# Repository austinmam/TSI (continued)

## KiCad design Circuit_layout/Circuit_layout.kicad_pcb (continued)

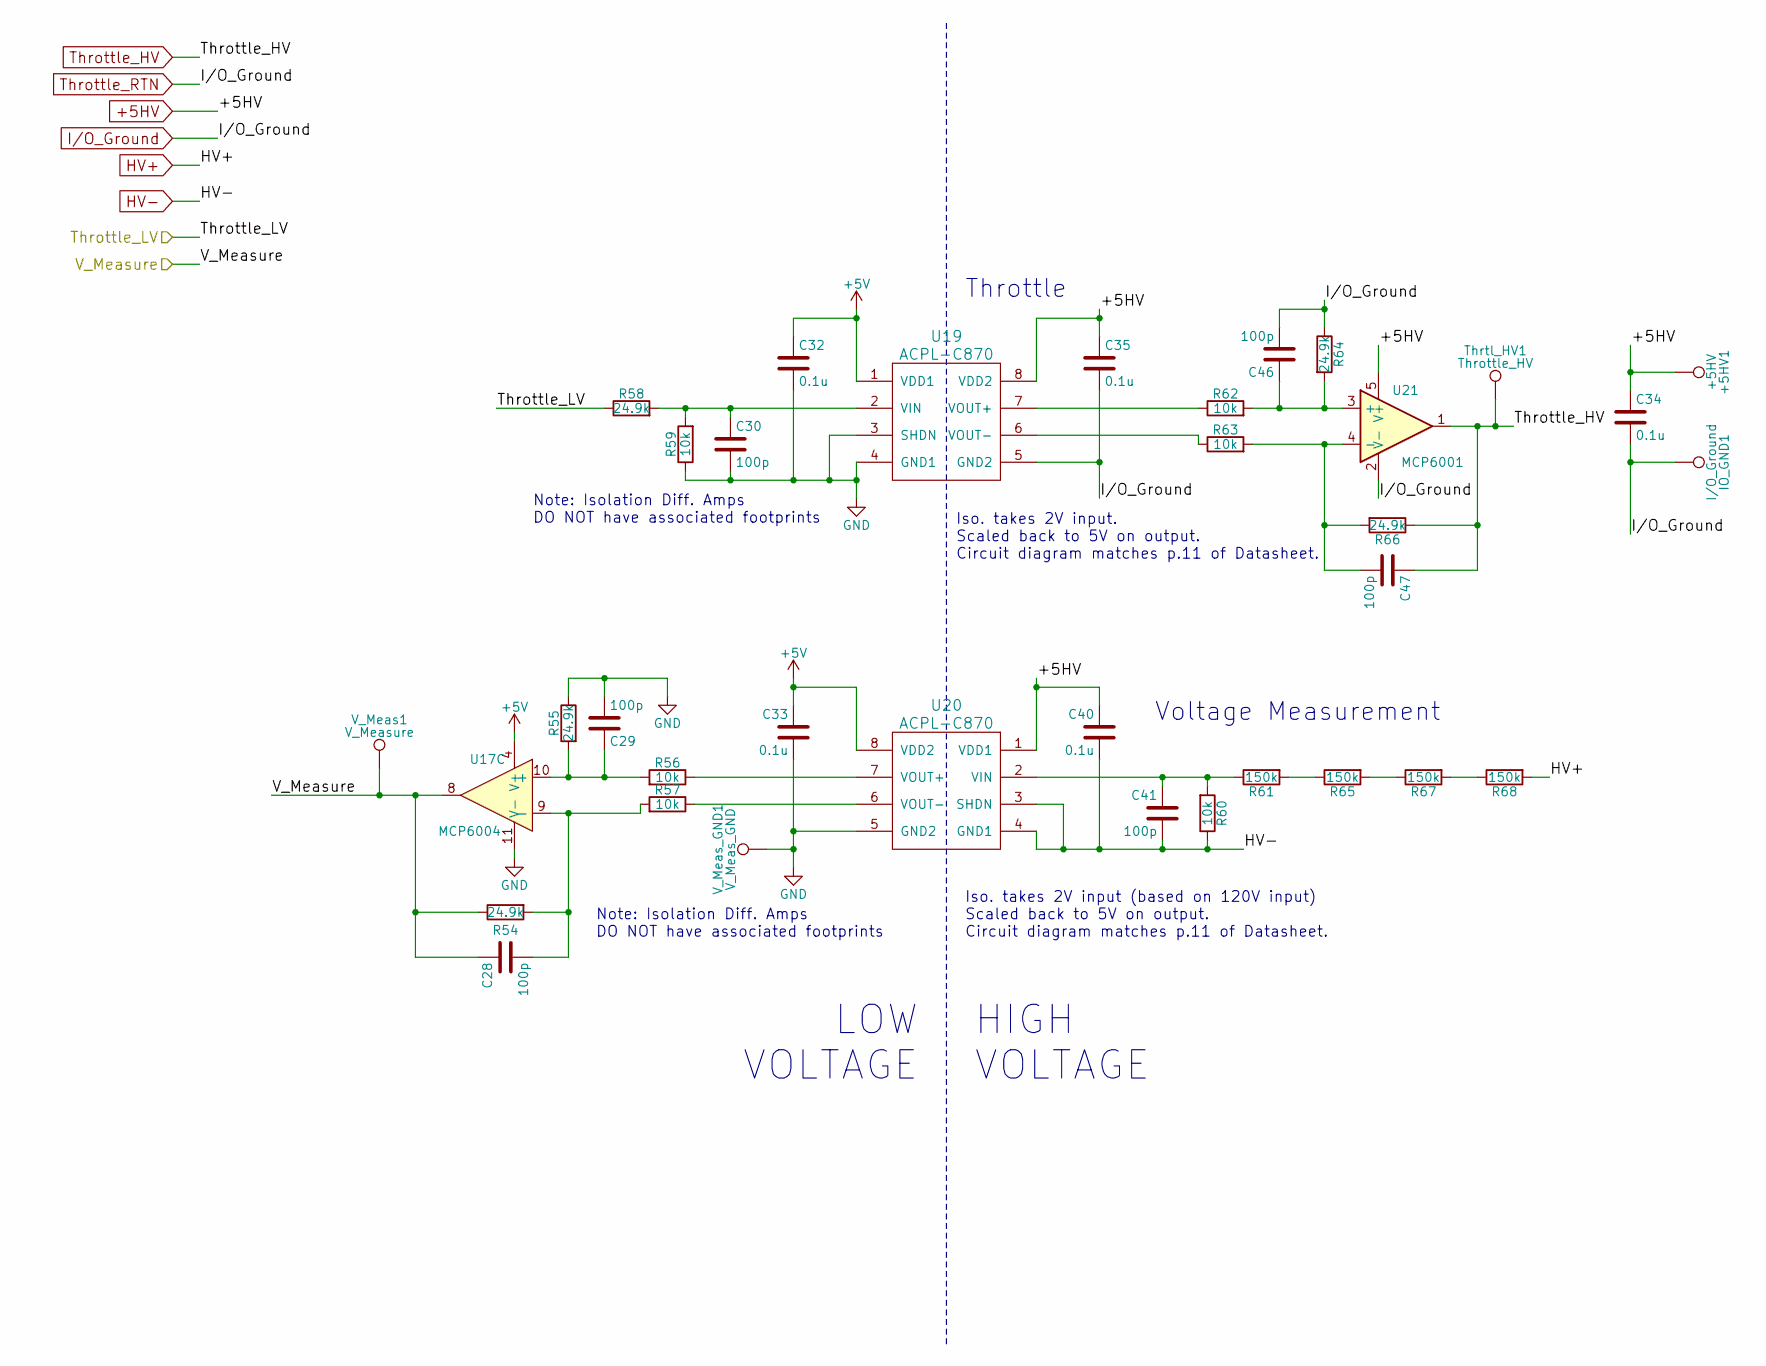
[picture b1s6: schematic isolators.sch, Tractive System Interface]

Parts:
+5HV1: +5HV; Measurement_Point_Round-SMD-Pad_Big
C28, C29, C30, C41, C46, C47: 100p; C_0805_HandSoldering; DigiKey P/N 399-1122-1-ND
C32, C33, C34, C35, C40: 0.1u; C_0805_HandSoldering; Digikey P/N 399-1168-1-ND
IO_GND1: I/O_Ground; Measurement_Point_Round-SMD-Pad_Big
R54, R55, R58, R64, R66: 24.9k; R_0805_HandSoldering; DigiKey P/N P24.9KCCT-ND
R56, R57, R59, R60, R62, R63: 10k; R_0805_HandSoldering; DigiKey P/N P10.0KCCT-ND
R61, R65, R67, R68: 150k; R_0805_HandSoldering; DigiKey P/N P150KCCT-ND
Thrtl_HV1: Throttle_HV; Measurement_Point_Round-SMD-Pad_Big
U17: MCP6004; SOIC-14_3.9x8.7mm_Pitch1.27mm; Digikey P/N MCP6004T-I/SLCT-ND
U19, U20: ACPL-C870; Iso_Diff_Amp_ACPL; Digikey P/N 516-2578-5-ND
U21: MCP6001; SOT-23-5_HandSoldering; DigiKey P/N MCP6001T-I/OTCT-ND
V_Meas1: V_Measure; Measurement_Point_Round-SMD-Pad_Big
V_Meas_GND1: V_Meas_GND; Measurement_Point_Square-SMD-Pad_Big

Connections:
+5HV: +5HV1.1, C34.1, C35.1, C40.1, U19.8 (VDD2), U20.1 (VDD1), U21.5 (V+); also elsewhere on the board
+5V: C32.1, C33.1, U17.4 (V+), U19.1 (VDD1), U20.8 (VDD2); also elsewhere on the board
/Isolators/Throttle_LV: R58.1; also elsewhere on the board
/Isolators/V_Measure: C28.1, R54.1, U17.8, V_Meas1.1; also elsewhere on the board
HV+: R68.2; also elsewhere on the board
HV-: C40.2, C41.2, R60.1, U20.3 (SHDN), U20.4 (GND1); also elsewhere on the board
I/O_Ground: C34.2, C35.2, C46.2, IO_GND1.1, R64.1, U19.5 (GND2), U21.2 (V-); also elsewhere on the board
unnamed: C28.2, R54.2, R57.2, U17.9 (-)
unnamed: C29.1, R55.2, R56.2, U17.10 (+)
unnamed: C30.1, R58.2, R59.2, U19.2 (VIN)
unnamed: C41.1, R60.2, R61.1, U20.2 (VIN)
unnamed: C46.1, R62.2, R64.2, U21.3 (+)
unnamed: C47.2, R63.2, R66.2, U21.4 (-)
unnamed: R56.1, U20.7 (VOUT+)
unnamed: R57.1, U20.6 (VOUT-)
unnamed: R61.2, R65.1
unnamed: R62.1, U19.7 (VOUT+)
unnamed: R63.1, U19.6 (VOUT-)
unnamed: R65.2, R67.1
unnamed: R67.2, R68.1
Throttle_HV: C47.1, R66.1, Thrtl_HV1.1, U21.1; also elsewhere on the board

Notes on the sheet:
Throttle
Voltage Measurement
HIGH VOLTAGE
LOW VOLTAGE
Iso. takes 2V input. Scaled back to 5V on output. Circuit diagram matches p.11 of Datasheet.
Note: Isolation Diff. Amps DO NOT have associated footprints
Iso. takes 2V input (based on 120V input) Scaled back to 5V on output. Circuit diagram matches p.11 of Datasheet.

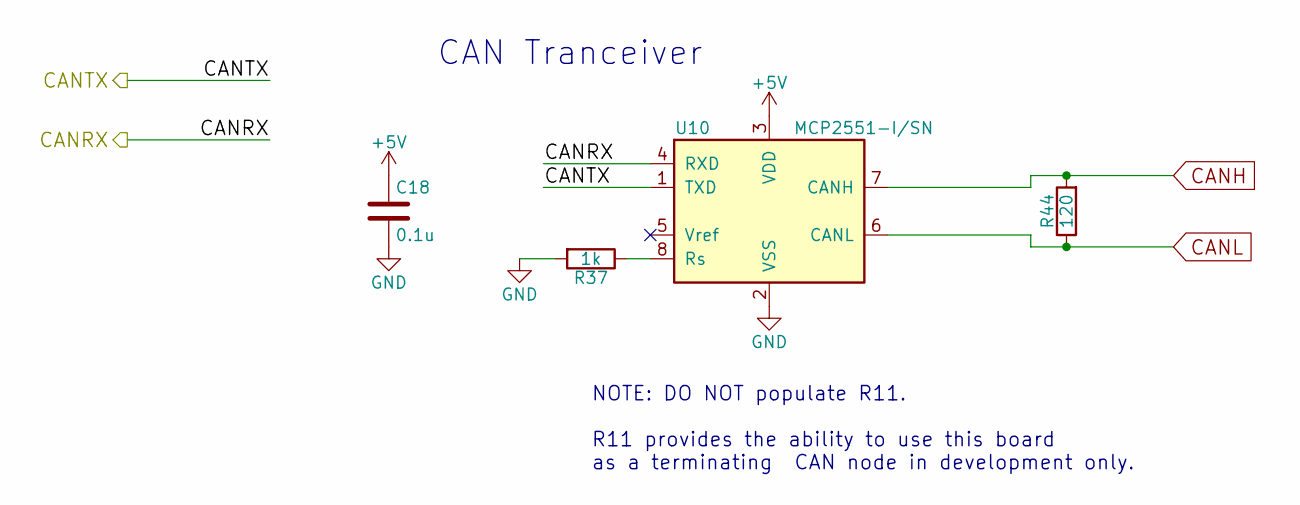
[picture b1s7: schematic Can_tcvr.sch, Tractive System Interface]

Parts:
C18: 0.1u; C_0805_HandSoldering; Digikey P/N 399-1168-1-ND
R37: 1k; R_0805_HandSoldering; DigiKey P/N P1.00KCCT-ND
R44: 120; R_0805_HandSoldering; DigiKey P/N 311-120CRCT-ND
U10: MCP2551-I/SN; SO-8; DigiKey P/N MCP2551-I/SN-ND

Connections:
+5V: C18.1, U10.3 (VDD); also elsewhere on the board
/CAN Transceiver/CANRX: U10.4 (RXD); also elsewhere on the board
/CAN Transceiver/CANTX: U10.1 (TXD); also elsewhere on the board
CANH: R44.2, U10.7 (CANH); also elsewhere on the board
CANL: R44.1, U10.6 (CANL); also elsewhere on the board
unnamed: R37.1, U10.8 (Rs)

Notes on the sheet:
CAN Tranceiver
NOTE: DO NOT populate R11. R11 provides the ability to use this board as a terminating CAN node in development only.

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
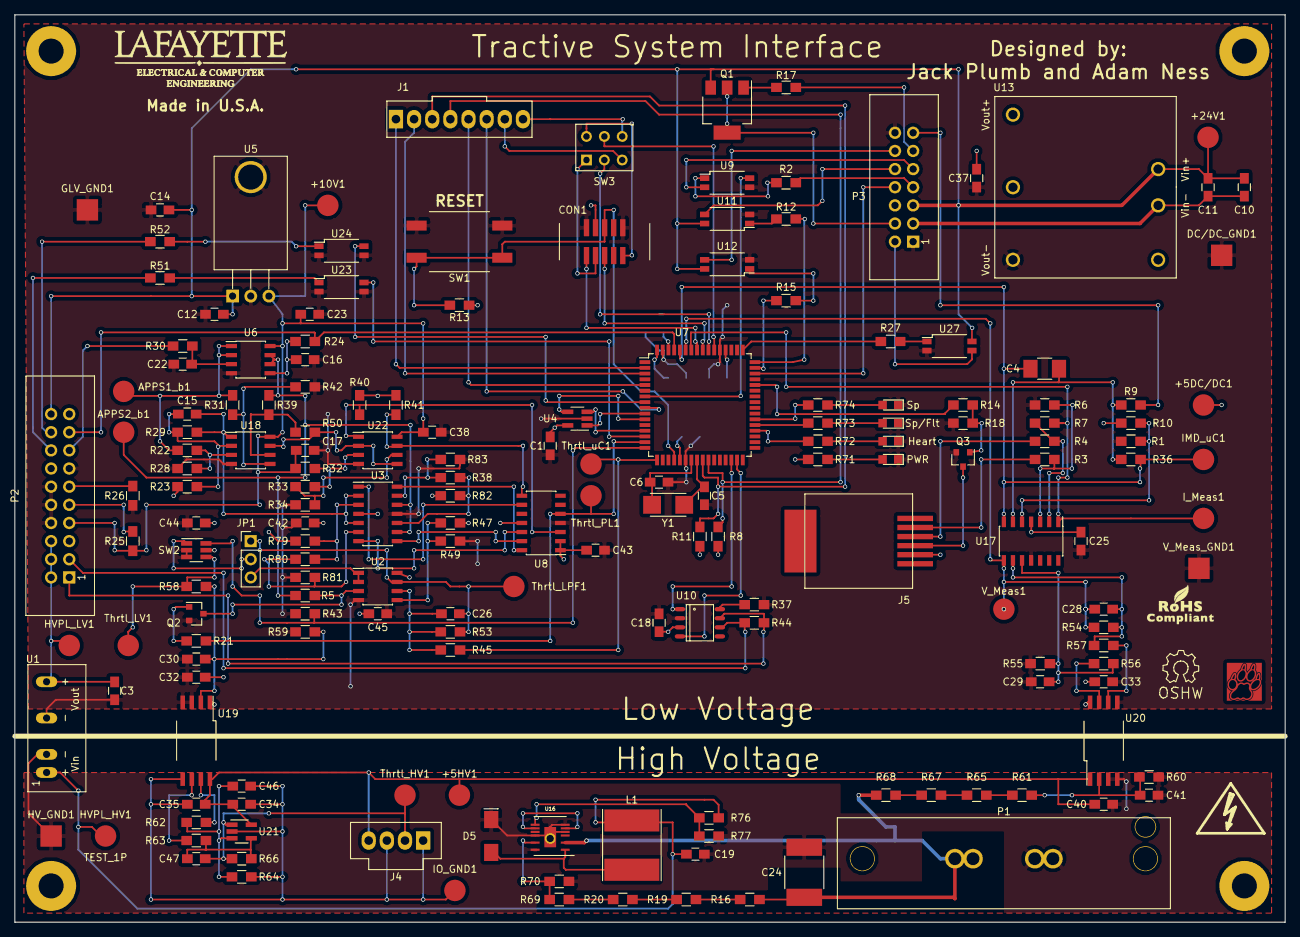
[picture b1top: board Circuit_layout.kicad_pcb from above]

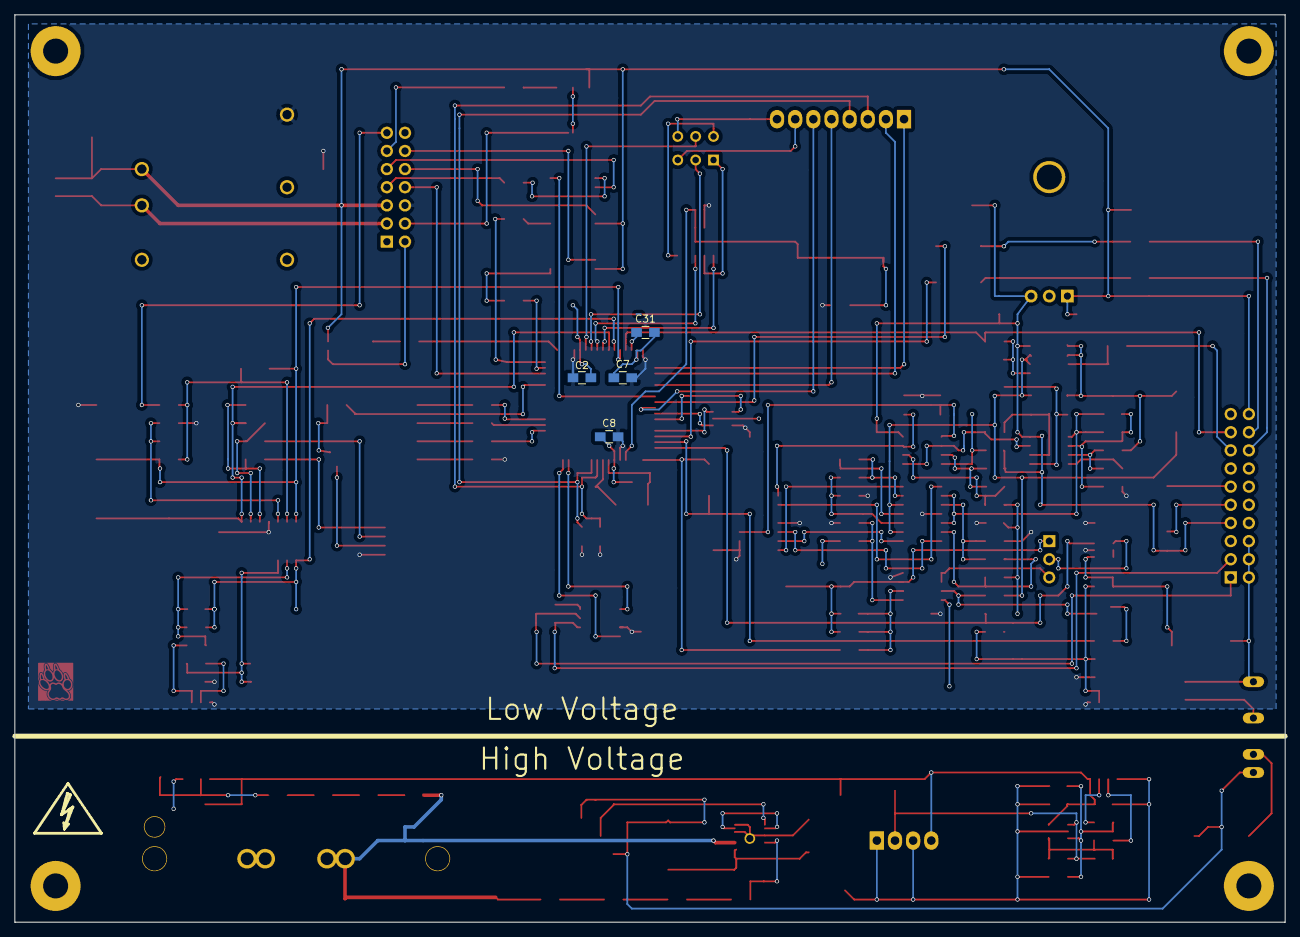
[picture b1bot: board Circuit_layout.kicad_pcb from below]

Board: 2 copper layers, 177.8 x 127.0 mm, 188 parts (4 on the bottom side), 138 nets.

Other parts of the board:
R27: 150; R_0805_HandSoldering
U14, U15, U25, U26: Mounting_hole; MountingHole_3.5mm_Pad
U27: TLP293; SOP-4_4.4x2.8mm_Pitch1.27mm
VAL: REF; lafLogo

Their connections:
+24V: U27.4; also elsewhere on the board
/Status Lights/CC_LED_CTRL: R27.2; also elsewhere on the board
unnamed: R27.1, U27.1

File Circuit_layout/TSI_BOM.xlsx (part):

Reference | Value | DigiKey P/N | URL | Man P/N | Description | Price
U13 | PDQ10-D | 102-3865-ND | http://www.digikey.com/product-detail/en/cui-inc/PDQ10-Q24-S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 | PDQ10-Q24-S5-D | DC/DC CONVERTER 5V 10W | 25.82
U1 | PDM2-S24-S12 | 102-2728-ND | https://www.digikey.com/product-detail/en/cui-inc/PDM2-S24-S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 | PDM2-S24-S12-S | CONVERT DC/DC 2W 12V 167MA OUT | 5.71
SW1 | SW_PUSH | 1715-1676-1-ND | http://www.digikey.com/products/en?keywords=ckn9363ct-nd | 1.14100.5030000 | SWITCH PUSH SPST-NO 0.1A 42V | 2.4
SW2 | TS5A3159-Q1 | 296-39512-1-ND | http://www.digikey.com/product-detail/en/texas-instruments/T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 | TS5A3159QDBVRQ1 | IC ANLG SW SPDT SOT23-6 | 0.98
U4 | LM95071-Q1 | 296-40259-1-ND | https://www.digikey.com/products/en/sensors-transducers/temp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 | LM95071QIMFX/NOPB | SENSOR TEMPERATURE SPI SOT23-5 | 2.9
U8 | 74ACT11030 | 296-4180-1-ND | http://www.digikey.com/product-detail/en/texas-instruments/7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 | 74ACT11030DR | IC GATE NAND 1CH 8-INP 14-SOIC | 2.2799999999999998
R44 | 120 | 311-120CRCT-ND | http://www.digikey.com/product-detail/en/yageo/RC0805FR-0712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 | RC0805FR-07120RL | RES SMD 120 OHM 1% 1/8W 0805 | 0.1
R12 | 150 | 311-150CRCT-ND | http://www.digikey.com/product-detail/en/yageo/RC0805FR-0715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 | RC0805FR-07150RL | RES SMD 150 OHM 1% 1/8W 0805 | 0.1
R15 | 150 | 311-150CRCT-ND | http://www.digikey.com/product-detail/en/yageo/RC0805FR-0715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 | RC0805FR-07150RL | RES SMD 150 OHM 1% 1/8W 0805 | 0.1
R27 | 150 | 311-150CRCT-ND | http://www.digikey.com/product-detail/en/yageo/RC0805FR-0715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 | RC0805FR-07150RL | RES SMD 150 OHM 1% 1/8W 0805 | 0.1
R70 | 47k | 311-47.0KCRCT-ND | http://www.digikey.com/product-detail/en/yageo/RC0805FR-0747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 | RC0805FR-0747KL | RES SMD 47K OHM 1% 1/8W 0805 | 0.1
C5 | 10p | 399-1108-1-ND | http://www.digikey.com/product-detail/en/kemet/C0805C100J5GA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 | C0805C100J5GACTU | CAP CER 10PF 50V NP0 0805 | 0.1
C6 | 10p | 399-1108-1-ND | http://www.digikey.com/product-detail/en/kemet/C0805C100J5GA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 | C0805C100J5GACTU | CAP CER 10PF 50V NP0 0805 | 0.1
C28 | 100p | 399-1122-1-ND | http://www.digikey.com/product-detail/en/kemet/C0805C101J5GA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 | C0805C101J5GACTU | CAP CER 100PF 50V NP0 0805 | 0.1
C29 | 100p | 399-1122-1-ND | http://www.digikey.com/product-detail/en/kemet/C0805C101J5GA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 | C0805C101J5GACTU | CAP CER 100PF 50V NP0 0805 | 0.1
C30 | 100p | 399-1122-1-ND | http://www.digikey.com/product-detail/en/kemet/C0805C101J5GA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 | C0805C101J5GACTU | CAP CER 100PF 50V NP0 0805 | 0.1
C41 | 100p | 399-1122-1-ND | http://www.digikey.com/product-detail/en/kemet/C0805C101J5GA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 | C0805C101J5GACTU | CAP CER 100PF 50V NP0 0805 | 0.1
C46 | 100p | 399-1122-1-ND | http://www.digikey.com/product-detail/en/kemet/C0805C101J5GA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 | C0805C101J5GACTU | CAP CER 100PF 50V NP0 0805 | 0.1
C47 | 100p | 399-1122-1-ND | http://www.digikey.com/product-detail/en/kemet/C0805C101J5GA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 | C0805C101J5GACTU | CAP CER 100PF 50V NP0 0805 | 0.1
C1 | 0.1u | 399-1168-1-ND | http://www.digikey.com/product-detail/en/kemet/C0805C104K3RA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 | C0805C104K3RACTU | CAP CER 0.1UF 25V X7R 0805 | 0.1
C12 | 0.1u | 399-1168-1-ND | http://www.digikey.com/product-detail/en/kemet/C0805C104K3RA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 | C0805C104K3RACTU | CAP CER 0.1UF 25V X7R 0805 | 0.1
C14 | 0.1u | 399-1168-1-ND | http://www.digikey.com/product-detail/en/kemet/C0805C104K3RA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 | C0805C104K3RACTU | CAP CER 0.1UF 25V X7R 0805 | 0.1
C15 | 0.1u | 399-1168-1-ND | http://www.digikey.com/product-detail/en/kemet/C0805C104K3RA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 | C0805C104K3RACTU | CAP CER 0.1UF 25V X7R 0805 | 0.1
C16 | 0.1u | 399-1168-1-ND | http://www.digikey.com/product-detail/en/kemet/C0805C104K3RA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 | C0805C104K3RACTU | CAP CER 0.1UF 25V X7R 0805 | 0.1
C17 | 0.1u | 399-1168-1-ND | http://www.digikey.com/product-detail/en/kemet/C0805C104K3RA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 | C0805C104K3RACTU | CAP CER 0.1UF 25V X7R 0805 | 0.1
C18 | 0.1u | 399-1168-1-ND | http://www.digikey.com/product-detail/en/kemet/C0805C104K3RA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 | C0805C104K3RACTU | CAP CER 0.1UF 25V X7R 0805 | 0.1
C2 | 0.1u | 399-1168-1-ND | http://www.digikey.com/product-detail/en/kemet/C0805C104K3RA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 | C0805C104K3RACTU | CAP CER 0.1UF 25V X7R 0805 | 0.1
C22 | 0.1u | 399-1168-1-ND | http://www.digikey.com/product-detail/en/kemet/C0805C104K3RA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 | C0805C104K3RACTU | CAP CER 0.1UF 25V X7R 0805 | 0.1
C23 | 0.1u | 399-1168-1-ND | http://www.digikey.com/product-detail/en/kemet/C0805C104K3RA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 | C0805C104K3RACTU | CAP CER 0.1UF 25V X7R 0805 | 0.1
C25 | 0.1u | 399-1168-1-ND | http://www.digikey.com/product-detail/en/kemet/C0805C104K3RA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 | C0805C104K3RACTU | CAP CER 0.1UF 25V X7R 0805 | 0.1
C26 | 0.1u | 399-1168-1-ND | http://www.digikey.com/product-detail/en/kemet/C0805C104K3RA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 | C0805C104K3RACTU | CAP CER 0.1UF 25V X7R 0805 | 0.1
C31 | 0.1u | 399-1168-1-ND | http://www.digikey.com/product-detail/en/kemet/C0805C104K3RA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 | C0805C104K3RACTU | CAP CER 0.1UF 25V X7R 0805 | 0.1
C32 | 0.1u | 399-1168-1-ND | http://www.digikey.com/product-detail/en/kemet/C0805C104K3RA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 | C0805C104K3RACTU | CAP CER 0.1UF 25V X7R 0805 | 0.1
C33 | 0.1u | 399-1168-1-ND | http://www.digikey.com/product-detail/en/kemet/C0805C104K3RA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 | C0805C104K3RACTU | CAP CER 0.1UF 25V X7R 0805 | 0.1
C34 | 0.1u | 399-1168-1-ND | http://www.digikey.com/product-detail/en/kemet/C0805C104K3RA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 | C0805C104K3RACTU | CAP CER 0.1UF 25V X7R 0805 | 0.1
C35 | 0.1u | 399-1168-1-ND | http://www.digikey.com/product-detail/en/kemet/C0805C104K3RA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 | C0805C104K3RACTU | CAP CER 0.1UF 25V X7R 0805 | 0.1
C37 | 0.1u | 399-1168-1-ND | http://www.digikey.com/product-detail/en/kemet/C0805C104K3RA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 | C0805C104K3RACTU | CAP CER 0.1UF 25V X7R 0805 | 0.1
C38 | 0.1u | 399-1168-1-ND | http://www.digikey.com/product-detail/en/kemet/C0805C104K3RA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 | C0805C104K3RACTU | CAP CER 0.1UF 25V X7R 0805 | 0.1
C40 | 0.1u | 399-1168-1-ND | http://www.digikey.com/product-detail/en/kemet/C0805C104K3RA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 | C0805C104K3RACTU | CAP CER 0.1UF 25V X7R 0805 | 0.1
C42 | 0.1u | 399-1168-1-ND | http://www.digikey.com/product-detail/en/kemet/C0805C104K3RA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 | C0805C104K3RACTU | CAP CER 0.1UF 25V X7R 0805 | 0.1
C43 | 0.1u | 399-1168-1-ND | http://www.digikey.com/product-detail/en/kemet/C0805C104K3RA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 | C0805C104K3RACTU | CAP CER 0.1UF 25V X7R 0805 | 0.1
C44 | 0.1u | 399-1168-1-ND | http://www.digikey.com/product-detail/en/kemet/C0805C104K3RA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 | C0805C104K3RACTU | CAP CER 0.1UF 25V X7R 0805 | 0.1
C45 | 0.1u | 399-1168-1-ND | http://www.digikey.com/product-detail/en/kemet/C0805C104K3RA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 | C0805C104K3RACTU | CAP CER 0.1UF 25V X7R 0805 | 0.1
C7 | 0.1u | 399-1168-1-ND | http://www.digikey.com/product-detail/en/kemet/C0805C104K3RA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 | C0805C104K3RACTU | CAP CER 0.1UF 25V X7R 0805 | 0.1
C8 | 0.1u | 399-1168-1-ND | http://www.digikey.com/product-detail/en/kemet/C0805C104K3RA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 | C0805C104K3RACTU | CAP CER 0.1UF 25V X7R 0805 | 0.1
SW3 | JS202011CQN | 401-2001-ND | http://www.digikey.com/product-detail/en/c-k/JS202011CQN/401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 | JS202011CQN | SWITCH SLIDE DPDT 300MA 6V | 0.41
D3 | Spare/Fault | 475-1278-1-ND | http://www.digikey.com/product-detail/en/osram-opto-semicond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 | LS R976-NR-1 | LED RED DIFFUSED 0805 SMD | 0.26
D1 | Power | 475-1410-1-ND | http://www.digikey.com/product-detail/en/osram-opto-semicond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 | LG R971-KN-1 | LED GREEN DIFFUSED 0805 SMD | 0.25
D2 | Heartbeat | 475-2560-1-ND | http://www.digikey.com/product-detail/en/osram-opto-semicond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 | LY R976-PS-36 | LED YELLOW DIFFUSED 0805 SMD | 0.35
C10 | 10uF | 490-10515-1-ND | http://www.digikey.com/product-detail/en/murata-electronics-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 | GRM21BR6YA106ME43L | CAP CER 10UF 35V X5R 0805 | 0.36
C11 | 10uF | 490-10515-1-ND | http://www.digikey.com/product-detail/en/murata-electronics-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 | GRM21BR6YA106ME43L | CAP CER 10UF 35V X5R 0805 | 0.36
C19 | 10uF | 490-10515-1-ND | http://www.digikey.com/product-detail/en/murata-electronics-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 | GRM21BR6YA106ME43L | CAP CER 10UF 35V X5R 0805 | 0.36
C24 | 1uF | 490-3550-1-ND | http://www.digikey.com/product-detail/en/murata-electronics-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 | GRM55DR72E105KW01L | CAP CER 1UF 250V X7R 2220 | 0.85
C4 | 47u | 490-6538-1-ND | http://www.digikey.com/product-detail/en/murata-electronics-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 | GRM32ER61C476KE15K | CAP CER 47UF 16V X5R 1210 | 0.86
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
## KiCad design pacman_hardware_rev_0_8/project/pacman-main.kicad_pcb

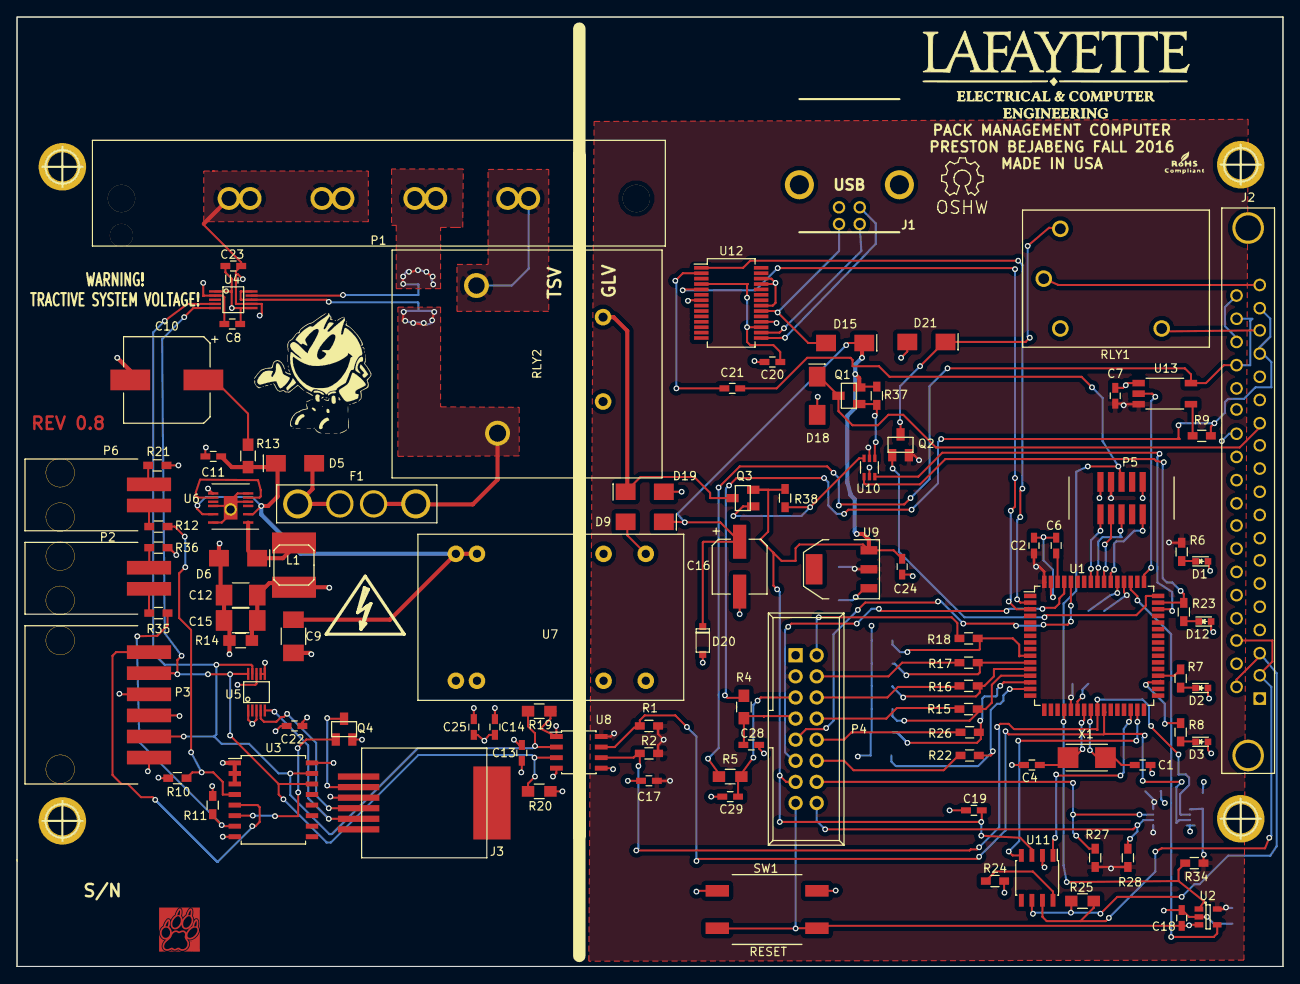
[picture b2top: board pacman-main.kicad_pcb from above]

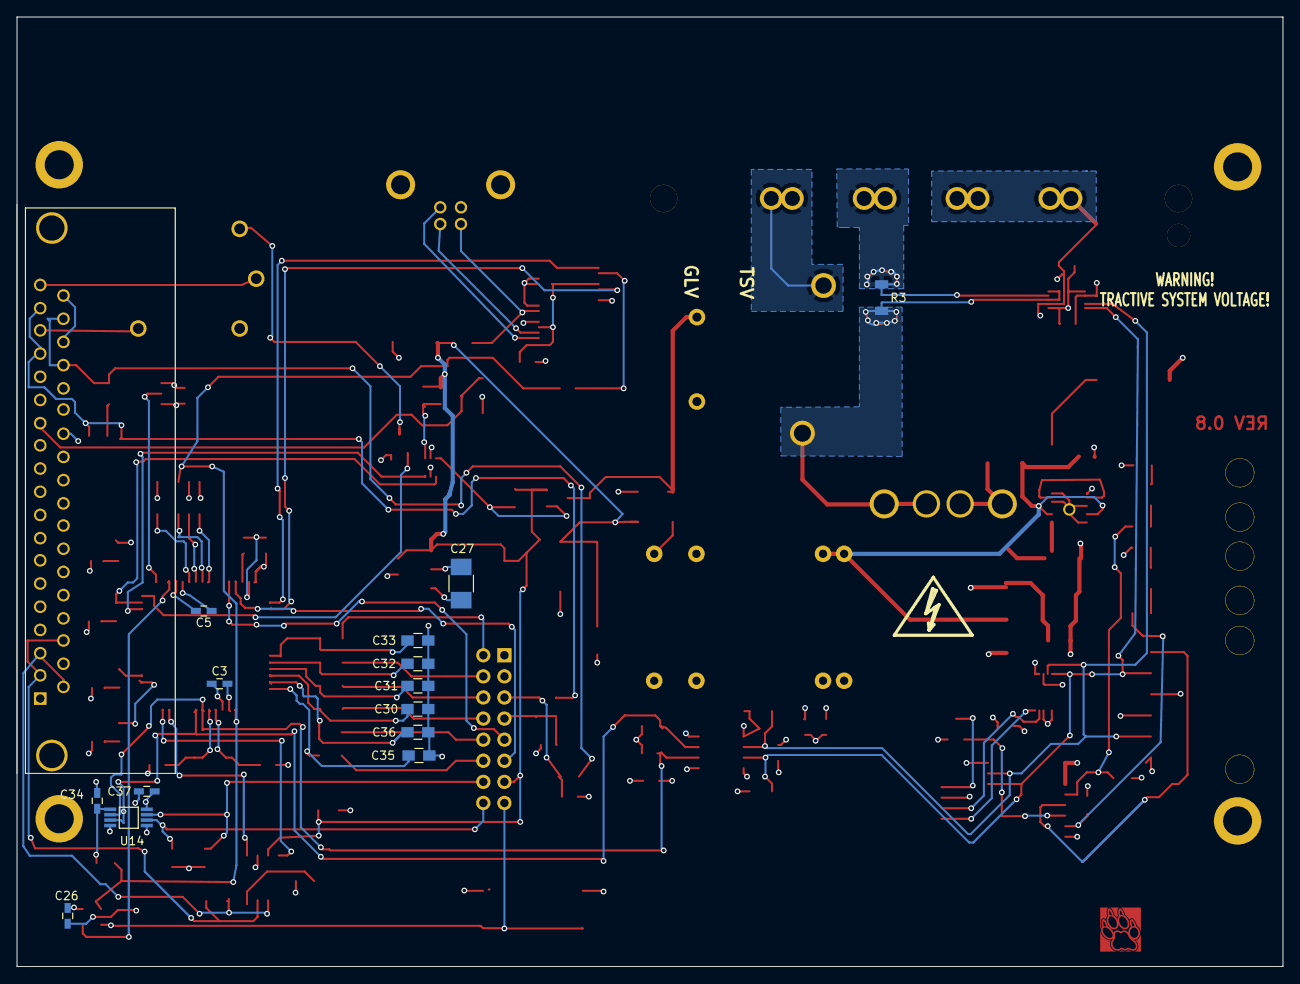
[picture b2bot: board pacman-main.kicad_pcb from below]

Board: 4 copper layers, 152.4 x 114.3 mm, 120 parts (14 on the bottom side), 90 nets.

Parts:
C1, C4: 10p; C_0603_HandSoldering
C2, C3, C5, C6, C7, C8, C13, C14, C17, C18, C19, C20, C21, C22, C23, C24, C25, C26: 0.1u; C_0603_HandSoldering
C9, C12, C15, C27: 10u; C_1210_HandSoldering
C10: 220u; c_elec_10x10
C11: 1u; C_0603_HandSoldering
C16: 220u; c_elec_6.3x7.7
C28, C29, C34, C37: .1u; C_0603_HandSoldering
C30, C31, C32, C33, C35, C36: 10u; C_0805_HandSoldering
D1: POWER; LED_0603
D2: FAULT; LED_0603
D3: SPARE; LED_0603
D5, D6, D9, D15, D18, D19, D21: SK310A-LTP; do214ac
D12: CHARGE; LED_0603
D20: NZH5V1B; sod123
F1: 5 A; blade_fuse_holder
J1: USB; conn_usb_B
J2: BACKPLANE CONNECTOR; DB37FD
J3: RJ12; MOLEX_RJ11
L1: 220u; SELF-WE-TPC_M
P1: POWER; AMPCONN_4POS
P2: CDETECT; MOLEX_HEADER_2POS
P3: EXT I2C; MOLEX_HEADER_6POS
P4: GPIO; IDC_Header_Straight_16pins
P5: JTAG
P6: LDETECT; MOLEX_HEADER_2POS
Q1, Q2, Q3, Q4: RRR015P03TL; sot346
R1, R2, R9, R10, R11, R27, R28, R34, R37, R38: 10k; R_0603_HandSoldering
R3: 0.001 1%; CSNL1206
R4, R5: 510; R_0805_HandSoldering
R6, R7, R8, R23, R24: 1k; R_0603_HandSoldering
R12, R21, R35, R36: 100; R_0603_HandSoldering
R13: 1 1%; R_0805_HandSoldering
R14, R19, R20: 1k; R_0805_HandSoldering
R15, R16, R17, R18, R22, R26: 510; R_0603_HandSoldering
R25: 120; R_0805_HandSoldering
RLY1: G5LE-1A4 DC3; relay_G5LE_1A4
RLY2: T9AS1D12-5; RLY_T9AS1D12-5
SW1: RESET; SW_RACON_8
U1: AT90CAN128-M; TQFP-64_14x14mm_Pitch0.8mm
U2: ADM6320; SOT-23-5
U3: PCF8574A; SOIC-16_7.5x10.3mm_Pitch1.27mm
U4: INA_226; msop_10_ads1015
U5: ADS1115; msop_10_ads1015
U6: LTC3638; TSSOP16_LTC3638
U7: NCS6S1205C
U8: Si8600; SOIC-8_3.9x4.9mm_Pitch1.27mm
U9: NCP1117ST33T3G; SOT-223
U10: SN74LVC2G06; DCK
U11: MCP2551-I/SN; SOIC-8_3.9x4.9mm_Pitch1.27mm
U12: FT232RL; SSOP-28_5.3x10.2mm_Pitch0.65mm
U13: TLP2361
U14: TCA9617B
VAL: REF; lafLogo
X1: 10MHz; crystal_TXC_7A
hole_3mm5, hole_3mm5#2, hole_3mm5#3, hole_3mm5#4: VAL**; hole_3mm5

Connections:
5V_AMPS: J3.5, Q4.3
5V_HV: C8.1, C12.1, C13.1, C14.1, C15.1, C22.1, C23.1, C25.1, L1.2, P3.3, Q4.2, R10.1, R11.2, R14.2, R19.2, R20.2, U3.16, U4.1, U4.6, U5.8, U6.9, U8.1
+3V3: C2.1, C3.1, C5.1, C7.1, C17.1, C26.1, C27.1, C34.1, C37.1, P4.3, P5.4, Q2.2, R1.1, R2.1, R6.2, R27.1, R28.1, R34.1, U1.21, U1.52, U1.64, U2.5, U8.8, U9.2, U10.5, U13.6, U14.1, U14.5, U14.8
+5V: C16.1, C19.1, C24.1, D9.2, D15.2, D20.2, P4.13, Q1.2, Q3.2, R37.2, R38.2, U9.3, U11.3
/CAN Transceiver/CANRX: U1.31, U11.4
/CAN Transceiver/CANTX: U1.30, U11.1
/External Connectors/PB0: C33.1, R18.1, U1.10
/External Connectors/PB1: C32.1, R17.1, U1.11
/External Connectors/PB2: C31.1, R16.1, U1.12
/External Connectors/PB3: C30.1, R15.1, U1.13
/External Connectors/PB4: C36.1, R26.1, U1.14
/External Connectors/PB5: C35.1, R22.1, U1.15
/External Connectors/PIN2: P4.2, R18.2
/External Connectors/PIN4: P4.4, R17.2
/External Connectors/PIN6: P4.6, R16.2
/External Connectors/PIN8: P4.8, R15.2
/External Connectors/PIN10: P4.10, R26.2
/External Connectors/PIN12: P4.12, R22.2
/External Connectors/SCL_IN: P4.14, R27.2, U14.7
/External Connectors/SDA_IN: P4.16, R28.2, U14.6
/External Connectors/SLOOP_A2: J2.35, J2.37
/FTDI USB UART/DTR: C21.1, U12.2
/FTDI USB UART/RXD: U1.3, U12.5
/FTDI USB UART/TXD: U1.2, U12.1
/Isolated Power Supply/HV_PWR: C9.1, C11.1, D5.2, R13.1, U6.3, U6.14, U7.22, U7.23
/PC0: R8.2, U1.35
/PC1: R7.2, U1.36
/Safety Loop Wiring/CHARGE_CTRL: R23.2, U1.47, U10.1
/Safety Loop Wiring/FAN_CTRL: U1.46, U10.3
/Safety Loop Wiring/SAFETY_CTRL: Q2.1, U1.48
/Safety Loop Wiring/~CHRG_CTRL: Q3.1, R38.1, U10.6
/Safety Loop Wiring/~FAN_CTRL: Q1.1, R37.1, U10.4
/WATCHDOG: U1.51, U2.4
ADC0: P4.11, U1.61
ADC1: P4.9, U1.60
AMS_RESET: P3.6, U3.5
BATT+: P1.3, R3.2, U4.9
CANH: J2.2, J2.22, R25.1, U11.7
CANL: J2.3, J2.20, R25.2, U11.6
CHARGE+: P1.4, RLY2.1
CURRENT_HV_1: J3.3, U5.4
CURRENT_HV_2: J3.2, U5.5
FAN+: D18.2, J2.13, Q1.3
GND: C1.2, C2.2, C3.2, C4.2, C5.2, C6.2, C7.2, C16.2, C17.2, C18.2, C19.2, C20.2, C24.2, C26.2, C27.2, C28.2, C29.2, C30.2, C31.2, C32.2, C33.2, C34.2, C35.2, C36.2, C37.2, D1.2, D2.2, D3.2, D12.2, D18.1, D19.1, D20.1, D21.1, J1.4, J1.5, J1.6, J2.31, P4.1, P5.2, P5.10, R24.2, RLY1.2, RLY2.2, SW1.2, U1.22, U1.53, U1.63, U2.2, U7.16, U8.5, U9.1, U10.2, U11.2, U12.7, U12.18, U12.21, U12.25, U12.26, U13.4, U14.4
LED+: C28.1, P4.7, R4.1
LED-: C29.1, P4.5, R5.2
unnamed: C1.1, U1.24, X1.1
unnamed: C4.1, U1.23, X1.2
unnamed: C6.1, U1.62
unnamed: C10.1, R13.2
unnamed: C20.1, U12.4, U12.17
unnamed: D1.1, R6.1
unnamed: D2.1, R7.1
unnamed: D3.1, R8.1
unnamed: D5.1, F1.2
unnamed: D6.2, L1.1, U6.1
unnamed: D9.1, U7.14
unnamed: D12.1, R23.1
unnamed: D19.2, Q3.3, RLY2.5
unnamed: D21.2, Q2.3, RLY1.5
unnamed: P2.1, R35.2
unnamed: P2.2, R36.2
unnamed: P6.1, R12.2
unnamed: P6.2, R21.2
unnamed: Q4.1, U3.6
unnamed: R9.1, U13.1
unnamed: R24.1, U11.8
unnamed: U6.7, U6.10
PACK+: F1.1, R3.1, RLY2.3, U4.8, U4.10
PACK-: C8.2, C9.2, C10.2, C11.2, C12.2, C13.2, C14.2, C15.2, C22.2, C23.2, C25.2, D6.1, J3.4, P1.1, P1.2, P3.1, P3.4, R14.1, R21.1, R36.1, U3.1, U3.2, U3.3, U3.8, U4.2, U4.7, U5.1, U5.3, U5.6, U5.7, U6.6, U6.8, U6.12, U6.16, U6.17, U7.2, U7.3, U8.4
SCL_HV: P3.5, R20.1, U3.14, U4.5, U5.10, U8.3
SDA_HV: P3.2, R19.1, U3.15, U4.4, U5.9, U8.2
SLOOP_A1: J2.19, RLY1.1
SLOOP_A3: J2.16, J2.18, R4.2, R9.2
SLOOP_A4: J2.34, J2.36, R5.1, U13.3
SLOOP_B1: J2.17, RLY1.3
SLOOP_DET: U1.49, U13.5
SW_SCL: R2.2, U1.25, U8.6, U14.2
SW_SDA: R1.2, U1.26, U8.7, U14.3
TCK: P5.1, U1.57
TDI: P5.9, U1.54
TDO: P5.3, U1.55
TMS: P5.5, U1.56
USBD+: J1.3, U12.15
USBD-: J1.2, U12.16
VUSB: D15.1, J1.1, U12.20
~CHRG_DET: R10.2, R12.1, U3.4
~LOW_DET: R11.1, R35.1, U3.7
~RESET: C18.1, P4.15, SW1.1, U2.3
~RESET_AVR: C21.2, P5.6, R34.2, U1.20, U2.1

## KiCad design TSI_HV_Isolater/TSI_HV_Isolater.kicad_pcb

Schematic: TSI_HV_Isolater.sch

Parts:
C1, C5, C9, C10, C11, C12, C13, C14: 0.1u; C_0603_HandSoldering; DigiKey P/N 311-1343-1-ND
C2, C18: 10u; C_0603_HandSoldering; DigiKey P/N 490-3298-1-ND
C3, C19: 22u; C_0603_HandSoldering; DigiKey P/N 490-7611-1-ND
C4, C6, C7: 1u; C_2220_HandSoldering; Digi-Key P/N 445-2304-1-ND
C8: 330p; C_0603_HandSoldering; DigiKey P/N 311-1186-1-ND
J1: CONN_01X02; TerminalBlock_Pheonix_MPT-5.08mm_2pol
J2: RJ12; MOLEX_RJ11; DigiKey P/N WM3789CT-ND
J3: CONN_01X10; TerminalBlock_Pheonix_MPT-5.08mm_10pol
J4: CONN_01X05; TerminalBlock_Pheonix_MPT-2.54mm_5pol
R1, R2, R5, R6, R7, R8, R9, R10: 10k; R_1206_HandSoldering; DigiKey P/N 311-10KERCT-ND
R11: 120; R_1206_HandSoldering; DigiKey P/N 311-120ERCT-ND
R12, R16, R17, R22, R23: 2k; R_0603_HandSoldering; DigiKey P/N 311-2.0KGRCT-ND
R13: 3k; R_0603_HandSoldering; DigiKey P/N 311-3.0KGRCT-ND
R14, R19, R25, R26: 4.99k; R_0603_HandSoldering; DigiKey P/N 311-4.99KHRCT-ND
R15: 20k; R_0603_HandSoldering; DigiKey P/N 311-20.0KHRCT-ND
U1: RDD08110S12; DigiKey P/N 1470-3083-5-ND
U2, U9: AZ1117CH-5.0TRG1; SOT-223_cus; DigiKey P/N AZ1117CH-5.0TRG1
U3, U8: MCP6001; MCP6001_SOT_23-5; DigiKey P/N MCP6001T-I/OTCT-ND
U4: TLP2361; FODM8701; DigiKey P/N TLP2361(TPLECT-ND
U5: AMC1100DWVR; amc1100_SOIC; DigiKey P/N 296-38822-5-ND
U6: ACPL-C870; amc1100_SOIC; DigiKey P/N 516-2578-5-ND
U10: place_holder; logo_lafayette_ece_24mmx9mm
U11: place_holder; lafLogo
U12: place_holder; rohs_symbol
U13: place_holder; Symbol_HighVoltage_Type2_FSilk_VerySmall
U16, U17, U18: place_holder; MountingHole_3.2mm_M3_Pad

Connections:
/24MC_RDYHV: J4.2, R15.1
/24MC_RDYLV: J3.2, U4.5
/+5HV: C1.2, C3.1, C9.1, C10.1, U2.2, U3.5 (V+), U5.1, U6.8; also elsewhere on the board
/+5LV: C5.2, C11.1, C12.1, C14.2, C19.1, J2.5, U4.6, U5.8, U6.1, U8.5 (V+), U9.2; also elsewhere on the board
/+12HV: C2.1, J4.3, U2.3
/+12LV: C18.1, J3.4, J3.5, U9.3
/A1_LV: J2.3, J3.7
/A2_LV: J2.2, J3.6
/GND: C5.1, C11.2, C12.2, C13.2, C14.1, C18.2, C19.2, J2.4, J3.8, R12.2, R25.1, U4.4, U5.5, U6.3, U6.4, U8.2 (V-), U9.1
/HV+: C4.2, C6.2, C7.2, J1.1, R1.1, U1.22, U1.23
/HV-: C4.1, C6.1, C7.1, J1.2, R2.1, U1.2, U1.3
/HV_LED+: J3.9, U1.14
/HV_LED-: J3.10, U1.16
/HV_MES: J3.3, R26.1, U8.1
/RTN: C1.1, C2.2, C3.2, C9.2, C10.2, J4.4, R19.1, U2.1, U3.2 (V-), U4.3, U5.4, U6.5
/Throttle_IN: J3.1, R13.2
/Throttle_OUT: J4.1, R14.1, U3.1
unnamed: C8.1, R9.2, R11.2, U5.2
unnamed: C8.2, R10.2, R11.1, U5.3
unnamed: C13.1, R12.1, R13.1, U6.2
unnamed: R1.2, R5.1
unnamed: R2.2, R6.1
unnamed: R5.2, R7.1
unnamed: R6.2, R8.1
unnamed: R7.2, R9.1
unnamed: R8.2, R10.1
unnamed: R14.2, R16.1
unnamed: R15.2, U4.1
unnamed 33: R17.1, R19.2, U6.7; also elsewhere on the board
unnamed: R17.2, U3.3 (+)
unnamed: R22.1, R26.2, U8.4 (-)
unnamed: R22.2, U5.6
unnamed 37: R23.1, R25.2, U8.3 (+); also elsewhere on the board
unnamed: R23.2, U5.7

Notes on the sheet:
This optical isolater is meant to take in the main contactor line and the coil return.
This op-amp is an isolated op-amp with a differential input and a differential output see datasheet for more information.
This is a diff-amp with 5/2 scaling to scale the output voltage to 5 volts
This buck steps down the high voltage present at the motor controller HV+ and HV- terminals to power the high voltage present light. It has a 12 volt output it turns on around 40 volts.
current sensor input.
This divider scales down the 150 volt input range down to the 200mV input range on the isolater. (you should check my math)
All screw terminal connectors must be replaced with actual connectors reference geoff nudge's pacman for this

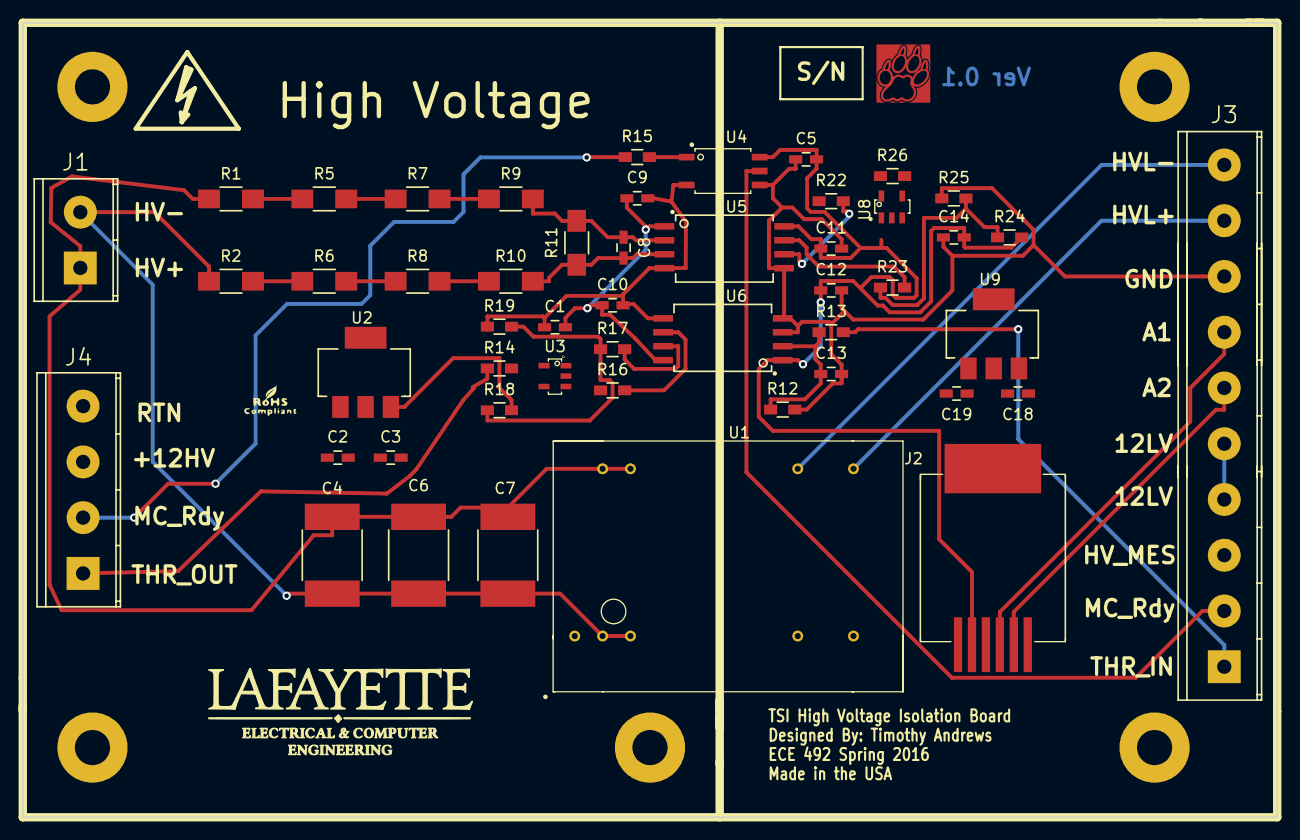
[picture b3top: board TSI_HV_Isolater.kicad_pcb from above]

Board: 2 copper layers, 114.3 x 72.4 mm, 59 parts (0 on the bottom side), 34 nets.

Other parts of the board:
R18, R24: 2k; R_0603_HandSoldering
U21, U30: place_holder; MountingHole_3.2mm_M3_Pad

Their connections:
/+5HV: R18.2; also elsewhere on the board
/+5LV: R24.2; also elsewhere on the board
unnamed 33: R18.1; also elsewhere on the board
unnamed 37: R24.1; also elsewhere on the board
